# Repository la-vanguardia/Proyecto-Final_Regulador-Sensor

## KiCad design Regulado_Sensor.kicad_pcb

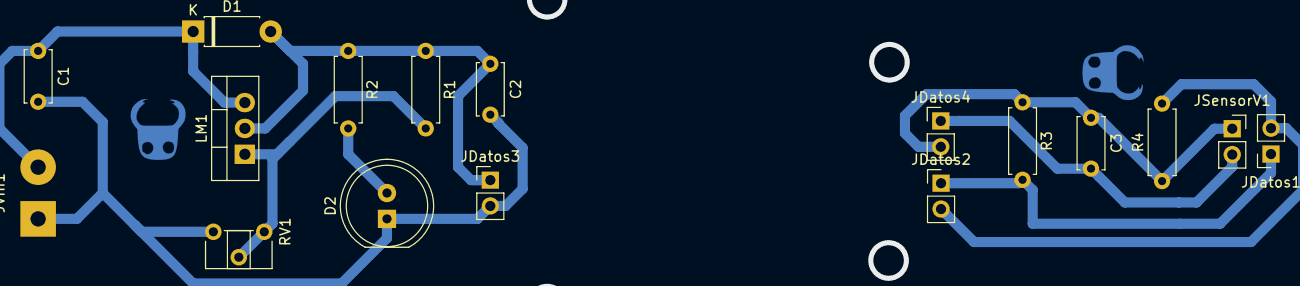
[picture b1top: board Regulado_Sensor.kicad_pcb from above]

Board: 2 copper layers, 17 parts (0 on the bottom side), 9 nets.

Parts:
C1, C2, C3: C; C_Disc_D5.0mm_W2.5mm_P5.00mm
D1: D; D_DO-41_SOD81_P7.62mm_Horizontal
D2: LED; LED_D8.0mm
JDatos1: Conn_01x02_Female; PinSocket_1x02_P2.54mm_Vertical
JDatos2, JDatos3, JDatos4: Conn_01x02_Female; PinHeader_1x02_P2.54mm_Vertical
JSensorV1: Conn_01x02_Female; PinSocket_1x02_P2.54mm_Vertical
JVin1: Conn_01x02_Female; SolderWirePad_1x02_P5.08mm_Drill1.5mm
LM1: LM317_3PinPackage; TO-220-3_Vertical
R1, R2, R3, R4: R; R_Axial_DIN0207_L6.3mm_D2.5mm_P7.62mm_Horizontal
RV1: R_POT_TRIM; Potentiometer_ACP_CA6-H2,5_Horizontal

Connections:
+5V: C1.1, D1.1, JVin1.2, LM1.3
GND: C1.2, C2.2, D2.1, JDatos3.2, JVin1.1, RV1.3
unnamed: C2.1, D1.2, JDatos3.1, LM1.2, R1.1, R2.1
unnamed: C3.1, JDatos4.2, JSensorV1.1, R3.1, R4.1
unnamed: C3.2, JDatos4.1, JSensorV1.2
unnamed: D2.2, R2.2
unnamed: JDatos1.1, JDatos2.1, R3.2
unnamed: JDatos1.2, JDatos2.2, R4.2
unnamed: LM1.1, R1.2, RV1.1, RV1.2

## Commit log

2019-12-06 Placas finalizadas
2019-12-08 Se arreglo un error en la placa de I2C
